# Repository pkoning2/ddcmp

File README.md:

# DDCMP Framer

This is a DDCMP synchronous link framer, connected to a host with a USB interface.

## Documentation

For detailed documentation, look in the `doc` subdirectory:

1. `api.md` -- programming interface for the framer.
2. `kicad.md` -- instructions for assembling the circuit board.
3. `software.md` -- how to build and load the firmware.
4. `design.md` -- design notes.

## Connections

To use the framer, connect the micro-USB board to a USB port on the computer that will control the framer.

There are a number of choices for connecting the synchronous link to whatever device you want to use it with:

1. To use a synchronous modem or modem eliminator, connect it with a straight through DB-25 cable to the male DB-25 (marked "DTE"), and operate the framer in "rs232_dte" mode.

2. To connect to a DDCMP device such as the DMR-11 using an RS-232 connection, connect its male DB-25 connector with a straight through DB-25 cable to the female DB-25 (marked "DCE") on the framer, and operate the framer in "rs232_dce" mode.  In this mode the framer supplies the bit clocks; you specify the desiredd data rate as one of the start command parameters.

3. If you have a device such as a DMR-11 that has a line card which is meant to connect to a BC55 bulkhead panel via a 40-pin ribbon cable, but you don't have or do not want to use a bulkhead panel, connect the line unit with 40 pin ribbon cable to the 40-pin header J8 (marked "To LU").  You can use either RS-232 (with bit clock generated by the framer) or integral modem operation using this connection.

4. If you want to connect the framer to a BC55 bulkhead panel (RS-232 or integral modem), connect the BC55 with a 40-pin ribbon cable to the 40-pin header J7.  Do not install termination resistors on the integral modem panel (BC55A); for details, refer to `doc/kicad.md`.

5. You can connect integral modem coaxial cables to BNC connectors J2 (incoming data) and J3 (outgoing data).  Note that DEC specifies triax cable (two shields) but those connectors are expensive so here we just use BNC connectors, which should be fine so long as you're not operating in an extremely noisy environment.  Do not install terminating resistors at the framer end, they are built in to the board.

## Indicator lights

There are three indicator lights on the framer board, as well as an LED on the Raspberry Pico board itself.  They are:

1. Pico board LED: "on" indicator.  It lights up when the framer is started with a successful start command, and off when the framer is stopped.

2. "SYN" indicator: byte sync status.  This lights up when the framer receiver has completed byte synchronization, having received four or more consecutive SYN bytes (hex 96).  SYN status remains set unless the DDCMP state machine restarts sync search; it will do so if a header CRC error occurs.  If the light does not come on, this may indicate no received signal, or (for integral modem mode) speed mismatch exceeding the 10% receive rate tolerance.  If the SYN indicator flashes frequently, this may indicate poor signal quality, or (for integral modem mode) a speed mismatch right at the limit of what the device can handle.  Note that the weak signal capability of the integral modem depends on the transformers used; refer to `doc/kicad.md` for details.

3. "RX" indicator: flashes when a frame is received (either successfully or with an error).

4. "TX" indicator: flashes when a frame is transmitted.

The RX and TX LEDs have pulse stretchers, so the light flashes are clearly visible even at low packet rates.

The RX and TX LEDs flash once when a framer start command is successfully executed.

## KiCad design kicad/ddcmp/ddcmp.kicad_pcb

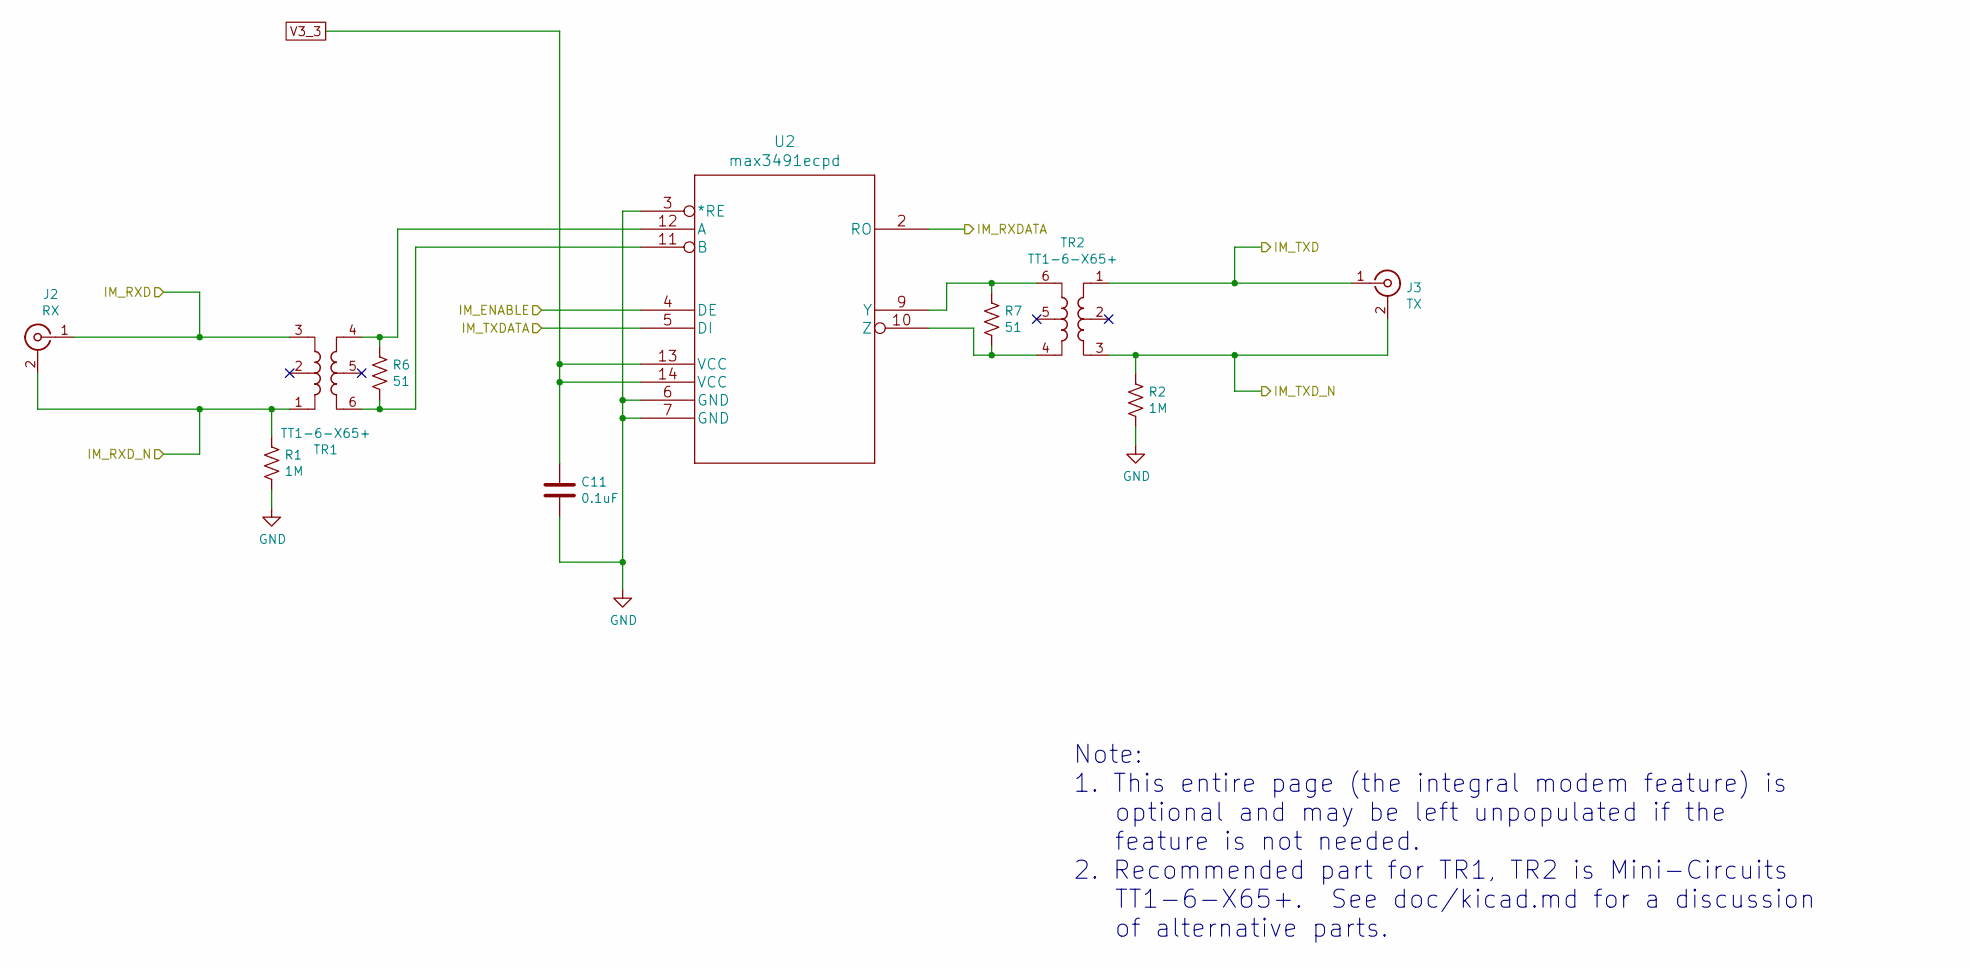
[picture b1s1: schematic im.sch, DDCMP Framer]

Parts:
C11: 0.1uF; C_Rect_L4.0mm_W2.5mm_P2.54mm; Digikey part 399-14010-1-ND
J2: RX; BNC_Molex_J_RA_PCB; Digikey part WM20430-ND
J3: TX; BNC_Molex_J_RA_PCB; Digikey part WM20430-ND
R1, R2: 1M; R_Axial_DIN0207_L6.3mm_D2.5mm_P10.16mm_Horizontal; Digikey part 1.0MQBK-ND
R6, R7: 51; R_Axial_DIN0207_L6.3mm_D2.5mm_P10.16mm_Horizontal; Digikey part 51QBK-ND
TR1, TR2: TT1-6-X65+; Mini-Circuits_CD637_X65
U2: max3491ecpd; DIP-14_W7.62mm; Digikey part MAX3491CPD+-ND

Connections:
/CPU/IM_ENABLE: U2.4 (DE); also elsewhere on the board
/CPU/IM_RXDATA: U2.2 (RO); also elsewhere on the board
/CPU/IM_TXDATA: U2.5 (DI); also elsewhere on the board
/Integral modem/IM_RXD: J2.1 (In), TR1.3; also elsewhere on the board
/Integral modem/IM_RXD_N: J2.2 (Ext), R1.1, TR1.1; also elsewhere on the board
/Integral modem/IM_TXD: J3.1 (In), TR2.1; also elsewhere on the board
/Integral modem/IM_TXD_N: J3.2 (Ext), R2.1, TR2.3; also elsewhere on the board
GND: C11.2, R1.2, R2.2, U2.3 (*RE), U2.6 (GND), U2.7 (GND); also elsewhere on the board
unnamed: R6.1, TR1.4, U2.12 (A)
unnamed: R6.2, TR1.6, U2.11 (B)
unnamed: R7.1, TR2.6, U2.9 (Y)
unnamed: R7.2, TR2.4, U2.10 (Z)
V3_3: C11.1, U2.13 (VCC), U2.14 (VCC); also elsewhere on the board

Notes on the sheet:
Note: 1. This entire page (the integral modem feature) is optional and may be left unpopulated if the feature is not needed. 2. Recommended part for TR1, TR2 is Mini-Circuits TT1-6-X65+. See doc/kicad.md for a discussion of alternative parts.

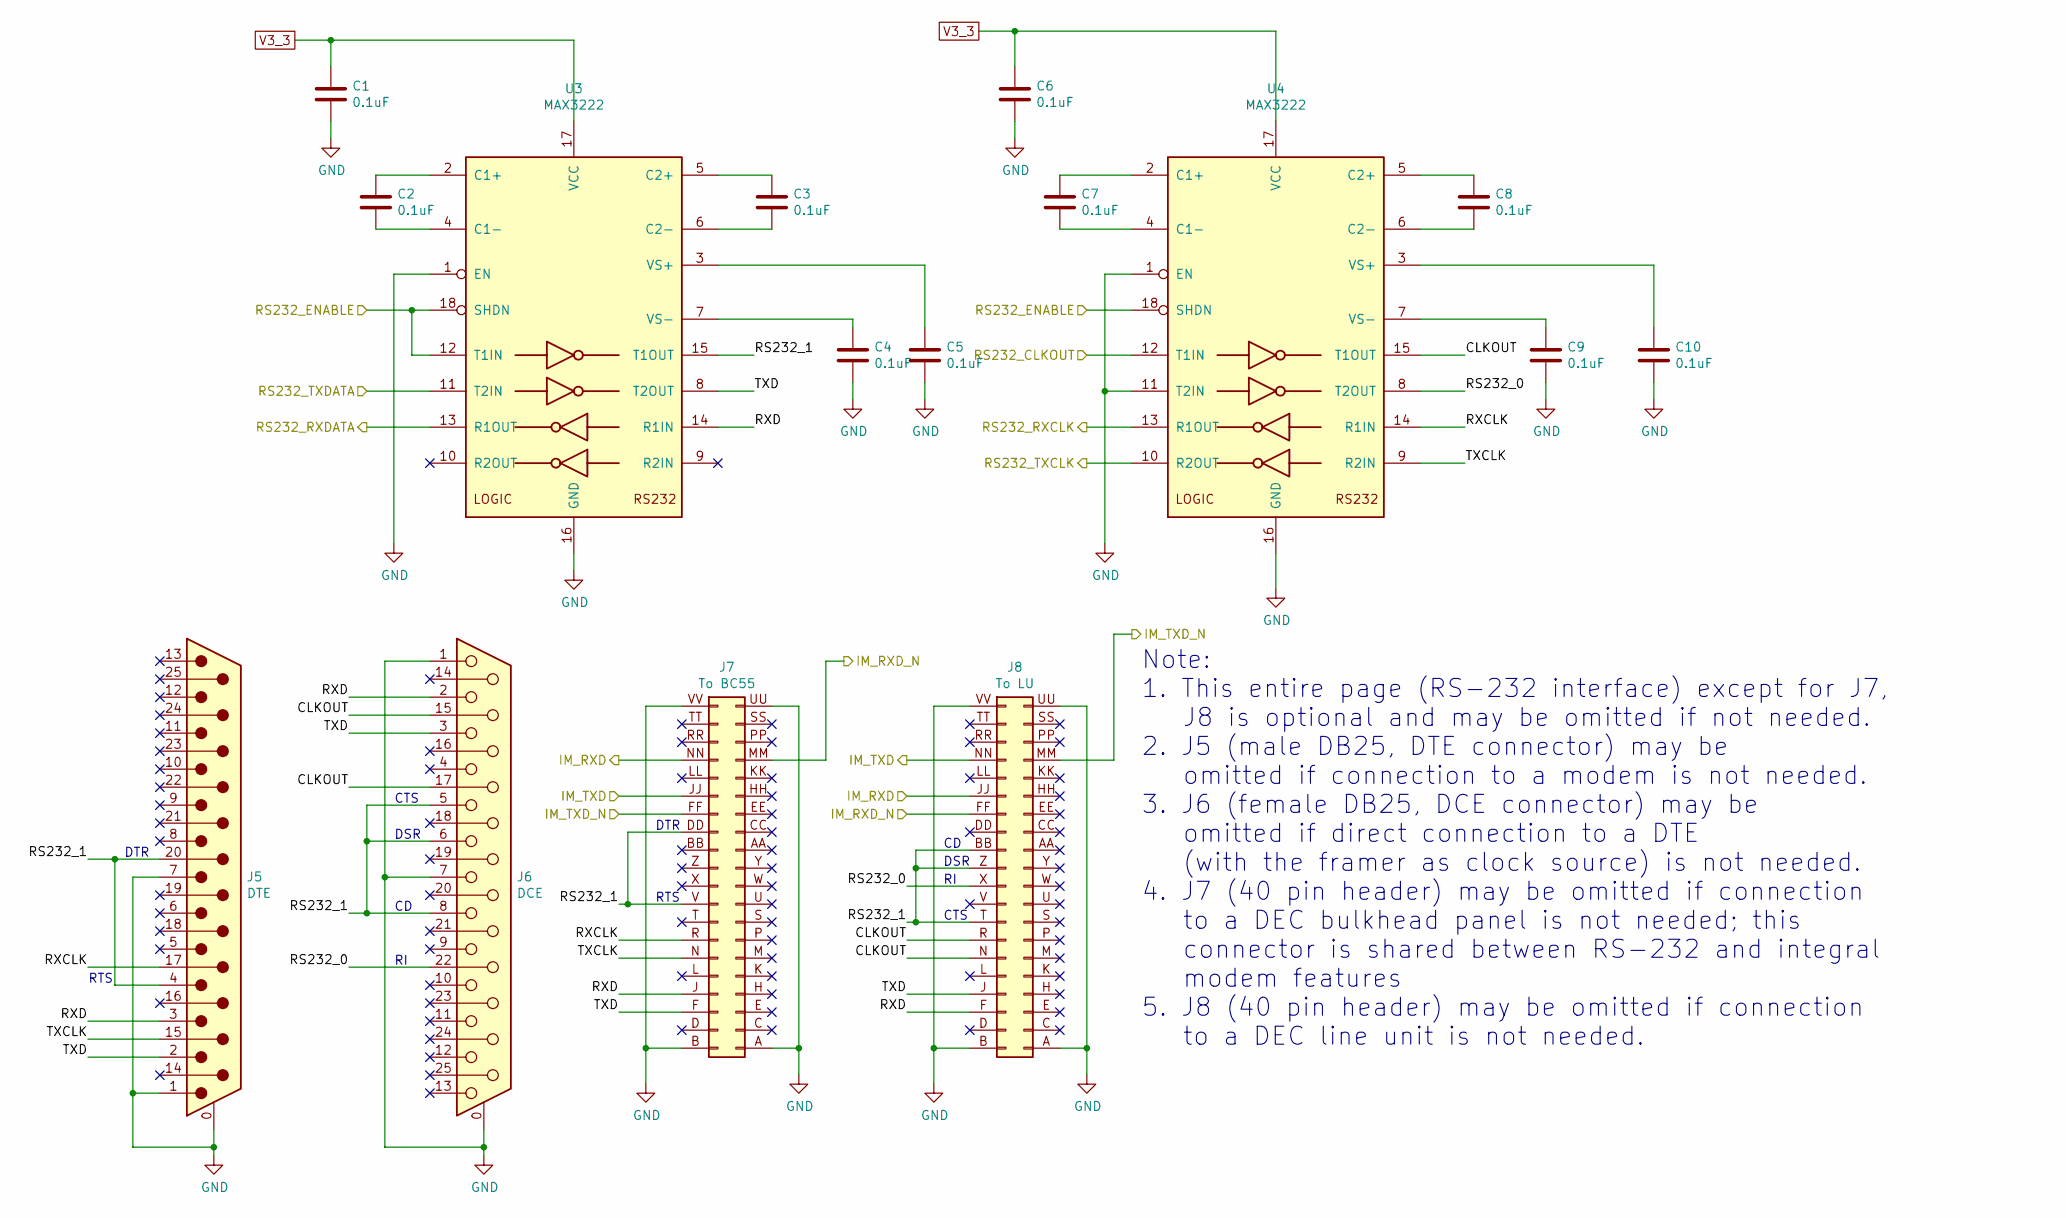
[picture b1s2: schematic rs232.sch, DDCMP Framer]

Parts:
C1, C2, C3, C4, C5, C6, C7, C8, C9, C10: 0.1uF; C_Rect_L4.0mm_W2.5mm_P2.54mm; Digikey part 399-14010-1-ND
J5: DTE; Amphenol_DB25M_PCB; Digikey part L717SDB25P1ACH4F-ND
J6: DCE; Amphenol_DB25F_PCB; Digikey part L77SDB25S1ACH3R-ND
J7: To BC55; Berg_40_pin_DEC_pinout; Digikey part 609-1779-ND
J8: To LU; Berg_40_pin_DEC_pinout; Digikey part 609-1779-ND
U3, U4: MAX3222; DIP-18_W7.62mm; Digikey part MAX3222ECPN+-ND

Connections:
/CPU/RS232_CLKOUT: U4.12 (T1IN); also elsewhere on the board
/CPU/RS232_ENABLE: U3.12 (T1IN), U3.18 (SHDN), U4.18 (SHDN); also elsewhere on the board
/CPU/RS232_RXCLK: U4.13 (R1OUT); also elsewhere on the board
/CPU/RS232_RXDATA: U3.13 (R1OUT); also elsewhere on the board
/CPU/RS232_TXCLK: U4.10 (R2OUT); also elsewhere on the board
/CPU/RS232_TXDATA: U3.11 (T2IN); also elsewhere on the board
/Integral modem/IM_RXD: J7.NN (Pin_7), J8.JJ (Pin_11); also elsewhere on the board
/Integral modem/IM_RXD_N: J7.MM (Pin_8), J8.FF (Pin_13); also elsewhere on the board
/Integral modem/IM_TXD: J7.JJ (Pin_11), J8.NN (Pin_7); also elsewhere on the board
/Integral modem/IM_TXD_N: J7.FF (Pin_13), J8.MM (Pin_8); also elsewhere on the board
/RS-232 I/O/CLKOUT: J6.15, J6.17, J8.N (Pin_29), J8.R (Pin_27), U4.15 (T1OUT)
/RS-232 I/O/RS232_0: J6.22, J8.X (Pin_21), U4.8 (T2OUT)
/RS-232 I/O/RS232_1: J5.4, J5.20, J6.5, J6.6, J6.8, J7.DD (Pin_15), J7.V (Pin_23), J8.BB (Pin_17), J8.T (Pin_25), J8.Z (Pin_19), U3.15 (T1OUT)
/RS-232 I/O/RXCLK: J5.17, J7.R (Pin_27), U4.14 (R1IN)
/RS-232 I/O/RXD: J5.3, J6.2, J7.J (Pin_33), J8.F (Pin_35), U3.14 (R1IN)
/RS-232 I/O/TXCLK: J5.15, J7.N (Pin_29), U4.9 (R2IN)
/RS-232 I/O/TXD: J5.2, J6.3, J7.F (Pin_35), J8.J (Pin_33), U3.8 (T2OUT)
GND: C1.2, C4.2, C5.2, C6.2, C9.2, C10.2, J5.0 (PAD), J5.1, J5.7, J6.0 (PAD), J6.1, J6.7, J7.A (Pin_40), J7.B (Pin_39), J7.UU (Pin_2), J7.VV (Pin_1), J8.A (Pin_40), J8.B (Pin_39), J8.UU (Pin_2), J8.VV (Pin_1), U3.1 (EN), U3.16 (GND), U4.1 (EN), U4.11 (T2IN), U4.16 (GND); also elsewhere on the board
unnamed: C2.1, U3.2 (C1+)
unnamed: C2.2, U3.4 (C1-)
unnamed: C3.1, U3.5 (C2+)
unnamed: C3.2, U3.6 (C2-)
unnamed: C4.1, U3.7 (VS-)
unnamed: C5.1, U3.3 (VS+)
unnamed: C7.1, U4.2 (C1+)
unnamed: C7.2, U4.4 (C1-)
unnamed: C8.1, U4.5 (C2+)
unnamed: C8.2, U4.6 (C2-)
unnamed: C9.1, U4.7 (VS-)
unnamed: C10.1, U4.3 (VS+)
V3_3: C1.1, C6.1, U3.17 (VCC), U4.17 (VCC); also elsewhere on the board

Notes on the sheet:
Note: 1. This entire page (RS-232 interface) except for J7, J8 is optional and may be omitted if not needed. 2. J5 (male DB25, DTE connector) may be omitted if connection to a modem is not needed. 3. J6 (female DB25, DCE connector) may be omitted if direct connection to a DTE (with the framer as cl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
RTS
DTR
DSR
CTS

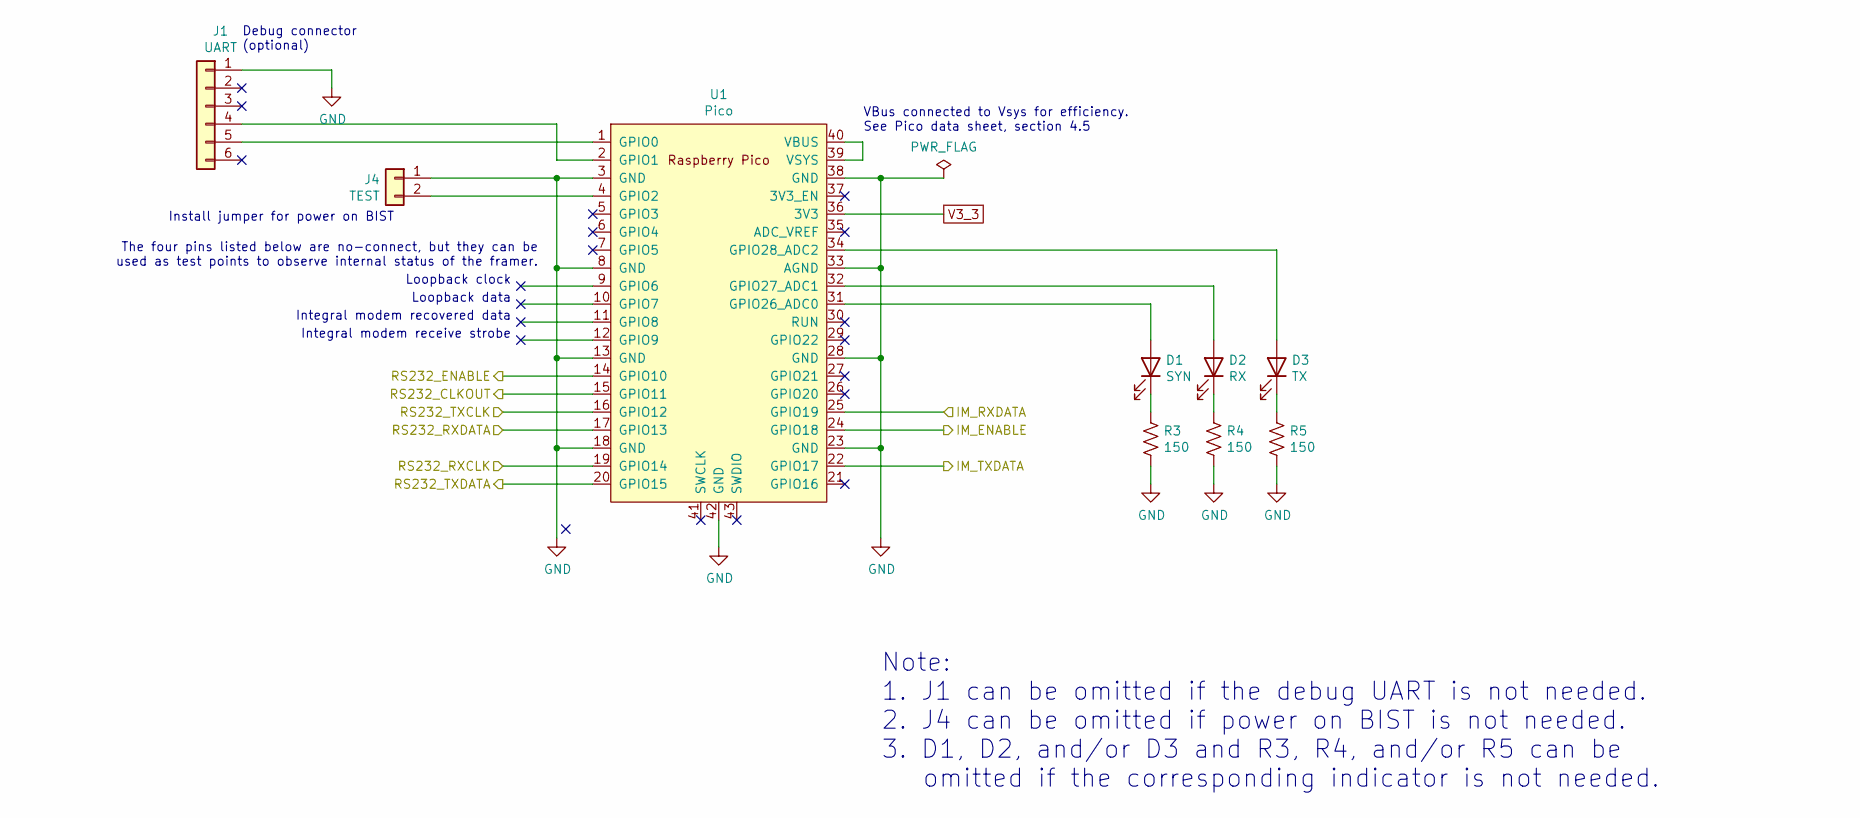
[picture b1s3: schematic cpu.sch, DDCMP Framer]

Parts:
D1: SYN; LED_D3.0mm; Digikey part 1497-1490-ND
D2: RX; LED_D3.0mm; Digikey part 1497-1492-ND
D3: TX; LED_D3.0mm; Digikey part 1497-1491-ND
J1: UART; Pin_Header_Straight_1x06_Pitch2.54mm; Digikey part 952-2269-ND
J4: TEST; Pin_Header_Straight_1x02_Pitch2.54mm; Digikey part 952-2261-ND
R3, R4, R5: 150; R_Axial_DIN0207_L6.3mm_D2.5mm_P10.16mm_Horizontal; Digikey part 150QBK-ND
U1: Pico; RPi_Pico_SMD_TH; Digikey part 2648-SC0915CT-ND

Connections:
/CPU/IM_ENABLE: U1.24 (GPIO18); also elsewhere on the board
/CPU/IM_RXDATA: U1.25 (GPIO19); also elsewhere on the board
/CPU/IM_TXDATA: U1.22 (GPIO17); also elsewhere on the board
/CPU/RS232_CLKOUT: U1.15 (GPIO11); also elsewhere on the board
/CPU/RS232_ENABLE: U1.14 (GPIO10); also elsewhere on the board
/CPU/RS232_RXCLK: U1.19 (GPIO14); also elsewhere on the board
/CPU/RS232_RXDATA: U1.17 (GPIO13); also elsewhere on the board
/CPU/RS232_TXCLK: U1.16 (GPIO12); also elsewhere on the board
/CPU/RS232_TXDATA: U1.20 (GPIO15); also elsewhere on the board
GND: J1.1, J4.1, R3.2, R4.2, R5.2, U1.3 (GND), U1.8 (GND), U1.13 (GND), U1.18 (GND), U1.23 (GND), U1.28 (GND), U1.33 (AGND), U1.38 (GND), U1.42 (GND); also elsewhere on the board
unnamed: D1.1 (K), R3.1
unnamed: D1.2 (A), U1.31 (GPIO26_ADC0)
unnamed: D2.1 (K), R4.1
unnamed: D2.2 (A), U1.32 (GPIO27_ADC1)
unnamed: D3.1 (K), R5.1
unnamed: D3.2 (A), U1.34 (GPIO28_ADC2)
unnamed: J1.4, U1.2 (GPIO1)
unnamed: J1.5, U1.1 (GPIO0)
unnamed: J4.2, U1.4 (GPIO2)
unnamed: U1.39 (VSYS), U1.40 (VBUS)
V3_3: U1.36 (3V3); also elsewhere on the board

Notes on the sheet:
Debug connector (optional)
VBus connected to Vsys for efficiency. See Pico data sheet, section 4.5
Loopback clock
Loopback data
Integral modem recovered data
Install jumper for power on BIST
Integral modem receive strobe
The four pins listed below are no-connect, but they can be used as test points to observe internal status of the framer.
Note: 1. J1 can be omitted if the debug UART is not needed. 2. J4 can be omitted if power on BIST is not needed. 3. D1, D2, and/or D3 and R3, R4, and/or R5 can be omitted if the corresponding indicator is not needed.

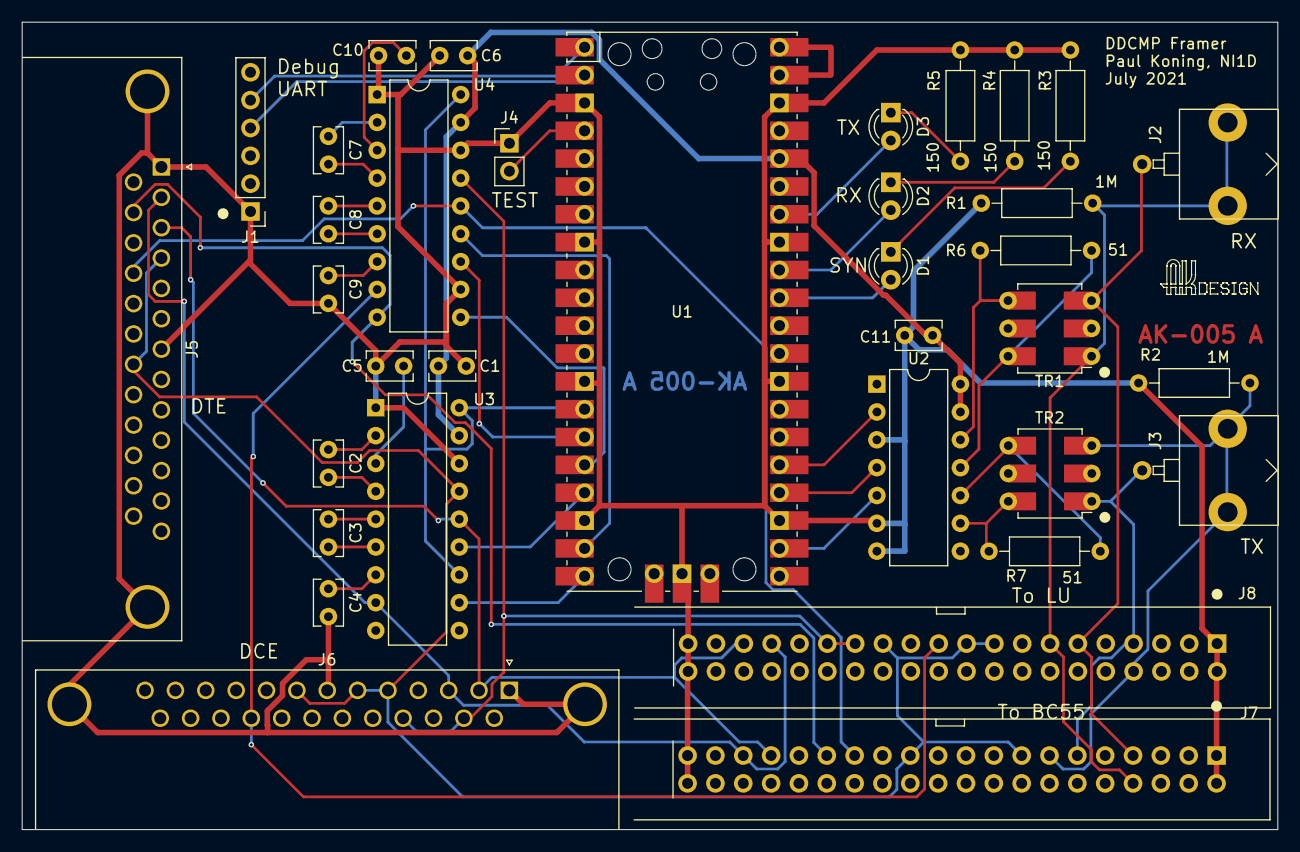
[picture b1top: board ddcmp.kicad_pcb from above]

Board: 2 copper layers, 114.6 x 73.7 mm, 35 parts (0 on the bottom side), 48 nets.

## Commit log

2021-05-18 Initial commit
    This is not yet complete and not working. The board layout hasn't
    started yet.
2021-05-18 Finish the connector hookups, to be verified carefully against DMR-11 schematics.
2021-05-21 Complete schematic, PCB layout, and matching code. Needs testing.
2021-05-26 Schematics tweaks, better 3d model for RPico.
2021-05-26 Bugfixes. This version now reliably runs built-in self test at full 1 Mb/s line speed.
2021-05-31 Bugfixes; add frequency measurement, raw transmit.
2021-05-31 Schematic and PCB modeling tweaks.
2021-06-03 Add Pico model from Nicolò Carandini
    For the original see https://github.com/ncarandini/KiCad-RP-Pico
2021-06-08 Schematics and 3d model cleanups; first drafts of a lot of documentation.
2021-06-08 Small cleanup.
2021-06-08 Add missing solder paste for Raspberry Pico footprint.
2021-06-10 Small schematics changes. Rewrite the integral modem receive demodulator state machine.
2021-07-07 Documentation improvements, small schematic fixes. Also firmware improvements, particularly clock rate accuracy.
2021-07-10 Add DMC11 compatibility mode; change transmit FIFO to be one byte wide.
2021-07-10 Small PCB tweaks. This version appears to be ready for fab.
2021-07-10 Turn off DEBUG.
2021-07-11 Add more detail on integral modem transformer options, based on new test results.
2021-07-11 Fix counters; in non-DEBUG mode some counters would not be seen due to counting them in CPU 1. Now they are counted as part of completed receive buffer handling in CPU 0.
2021-07-11 A better fix to the previous issue. It wasn't caching; it's a missing memory barrier causing CPU 1 to keep some state in registers that needs to go to memory for CPU 0 to see it.
2021-07-15 Do transmit DMA control (initiate DMA, handle completion) in the CPU 1 polling loop rather than by CPU 0 interrupts. This makes the code substantially simpler since the main control code no longer ha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
2021-08-23 Bugfixes in firmware, add status report on SYN status change. Update documentation. Add links for OSHPark shared PCB layout and Digikey shared BOM.
2021-08-23 Layout fixes; fix typo.
2021-09-16 1. Change transmit frame format to include a space for header CRC, so SIMH standard frame formatting works unchanged. The HCRC is still generated, though. 2. Change MAC addresses to be random AA-00-0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
2021-10-17 1. Add bit clock monitor and abort frame reception if clock is lost. 2. Make frequency measurement better for integral modem case. 3. New test mode: raw waveform (for integral modem).
2021-12-25 Fix description of test point on page 4 of the schematic.
2021-12-31 Clarify the way framer MAC addresses are constructed.
2022-09-12 Remove some obsolete text, refer to api.md instead
2024-01-10 Fix tud_network_can_xmit calls to add missing argument. An error not detected previously, or an API change? Not clear.

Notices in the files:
kicad/ddcmp/cpu.sch:
Copyright © 2021 by Paul Koning, NI1D
